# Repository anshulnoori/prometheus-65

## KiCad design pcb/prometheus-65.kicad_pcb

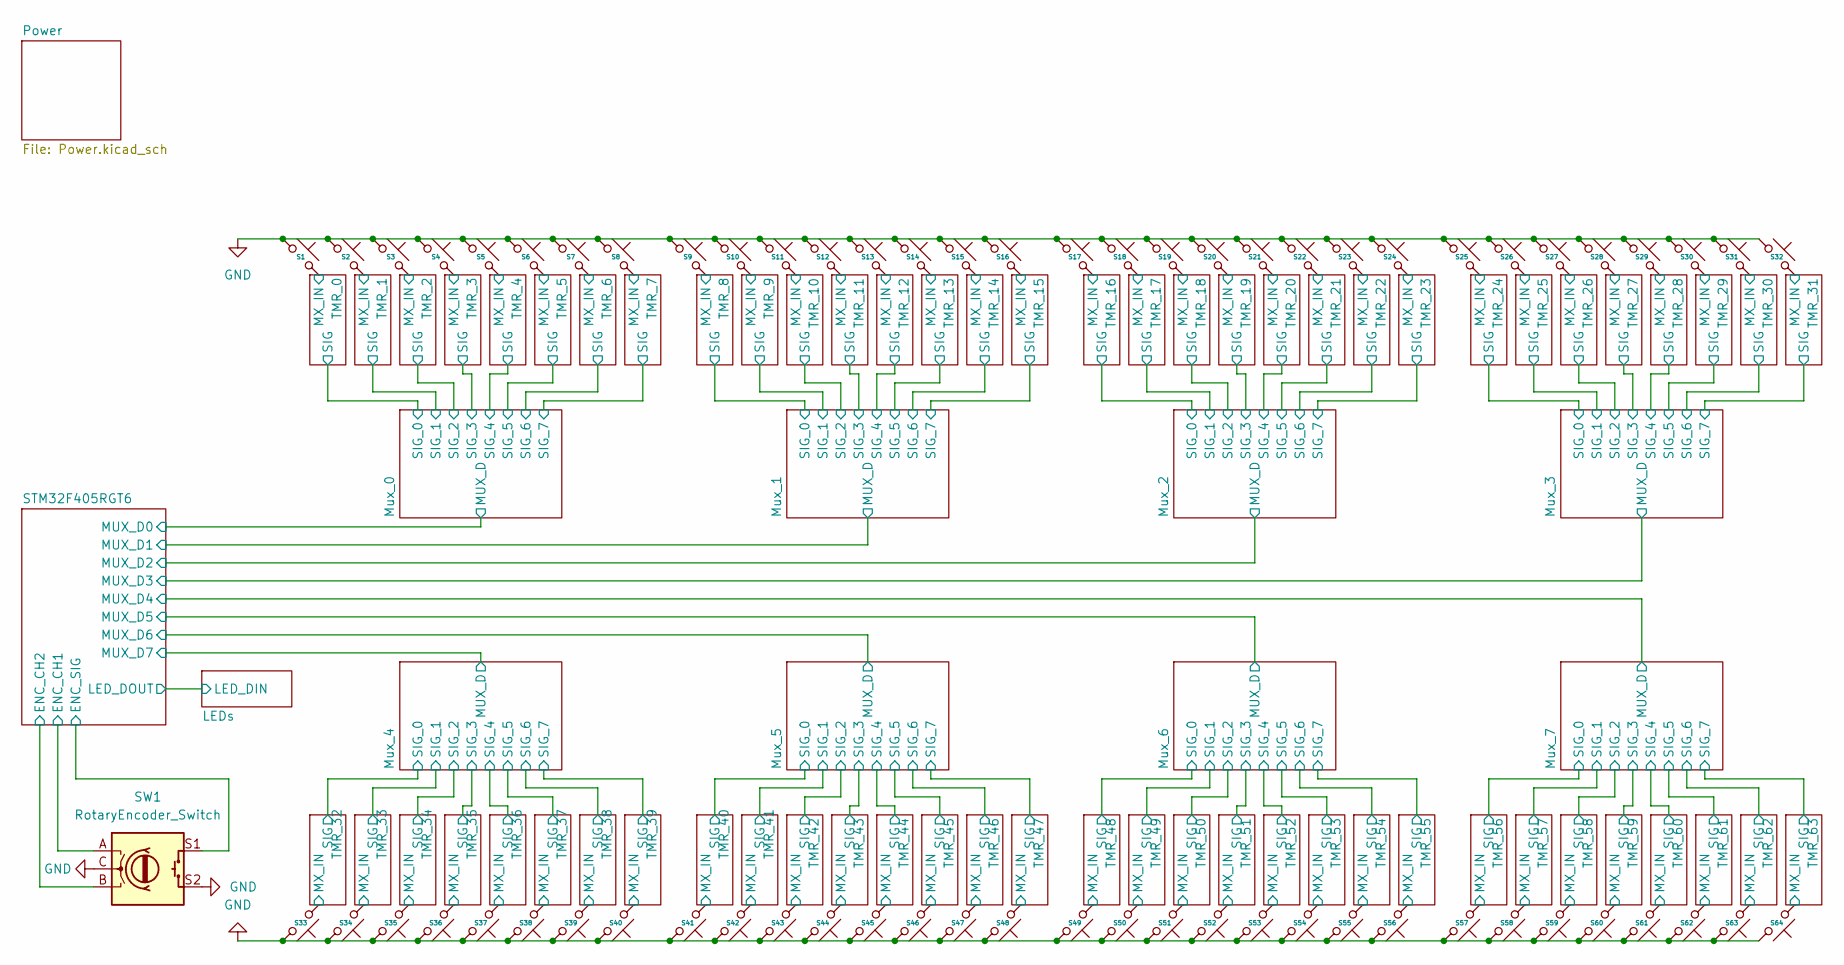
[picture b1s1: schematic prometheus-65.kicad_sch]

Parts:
S1, S2, S3, S4, S6, S7, S9, S10, S12, S13, S17, S18, S19, S20, S21, S22, S23, S24, S25, S26, S27, S28, S29, S30, S31, S33, S34, S35, S36, S37, S38, S39, S40, S41, S42, S43, S44, S45, S46, S47, S49, S50, S51, S53, S54, S55, S58, S60, S64: Hotswap_MX_Plated_1.00u
S5, S56: Hotswap_MX_Plated_1.50u
S8: Hotswap_MX_Plated_1.75u
S11, S57: Hotswap_MX_Plated_2.25u
S14, S15, S16, S48, S61, S62, S63: Hotswap_MX_Plated_1.25u
S32: Hotswap_MX_Plated_6.25u
S52: Hotswap_MX_Plated_2.00u
S59: Hotswap_MX_Plated_2.75u
SW1: RotaryEncoder_Switch; RotaryEncoder_Alps_EC11E-Switch_Vertical_H20mm

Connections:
/Mux_0/SIG_0: S1.2; also elsewhere on the board
/Mux_0/SIG_1: S2.2; also elsewhere on the board
/Mux_0/SIG_2: S3.2; also elsewhere on the board
/Mux_0/SIG_3: S4.2; also elsewhere on the board
/Mux_0/SIG_4: S5.2; also elsewhere on the board
/Mux_0/SIG_5: S6.2; also elsewhere on the board
/Mux_0/SIG_6: S7.2; also elsewhere on the board
/Mux_0/SIG_7: S8.2; also elsewhere on the board
/Mux_1/SIG_0: S9.2; also elsewhere on the board
/Mux_1/SIG_1: S10.2; also elsewhere on the board
/Mux_1/SIG_2: S11.2; also elsewhere on the board
/Mux_1/SIG_3: S12.2; also elsewhere on the board
/Mux_1/SIG_4: S13.2; also elsewhere on the board
/Mux_1/SIG_5: S14.2; also elsewhere on the board
/Mux_1/SIG_6: S15.2; also elsewhere on the board
/Mux_1/SIG_7: S16.2; also elsewhere on the board
/Mux_2/SIG_0: S17.2; also elsewhere on the board
/Mux_2/SIG_1: S18.2; also elsewhere on the board
/Mux_2/SIG_2: S19.2; also elsewhere on the board
/Mux_2/SIG_3: S20.2; also elsewhere on the board
/Mux_2/SIG_4: S21.2; also elsewhere on the board
/Mux_2/SIG_5: S22.2; also elsewhere on the board
/Mux_2/SIG_6: S23.2; also elsewhere on the board
/Mux_2/SIG_7: S24.2; also elsewhere on the board
/Mux_3/SIG_0: S25.2; also elsewhere on the board
/Mux_3/SIG_1: S26.2; also elsewhere on the board
/Mux_3/SIG_2: S27.2; also elsewhere on the board
/Mux_3/SIG_3: S28.2; also elsewhere on the board
/Mux_3/SIG_4: S29.2; also elsewhere on the board
/Mux_3/SIG_5: S30.2; also elsewhere on the board
/Mux_3/SIG_6: S31.2; also elsewhere on the board
/Mux_3/SIG_7: S32.2; also elsewhere on the board
/Mux_4/SIG_0: S33.2; also elsewhere on the board
/Mux_4/SIG_1: S34.2; also elsewhere on the board
/Mux_4/SIG_2: S35.2; also elsewhere on the board
/Mux_4/SIG_3: S36.2; also elsewhere on the board
/Mux_4/SIG_4: S37.2; also elsewhere on the board
/Mux_4/SIG_5: S38.2; also elsewhere on the board
/Mux_4/SIG_6: S39.2; also elsewhere on the board
/Mux_4/SIG_7: S40.2; also elsewhere on the board
/Mux_5/SIG_0: S41.2; also elsewhere on the board
/Mux_5/SIG_1: S42.2; also elsewhere on the board
/Mux_5/SIG_2: S43.2; also elsewhere on the board
/Mux_5/SIG_3: S44.2; also elsewhere on the board
/Mux_5/SIG_4: S45.2; also elsewhere on the board
/Mux_5/SIG_5: S46.2; also elsewhere on the board
/Mux_5/SIG_6: S47.2; also elsewhere on the board
/Mux_5/SIG_7: S48.2; also elsewhere on the board
/Mux_6/SIG_0: S49.2; also elsewhere on the board
/Mux_6/SIG_1: S50.2; also elsewhere on the board
/Mux_6/SIG_2: S51.2; also elsewhere on the board
/Mux_6/SIG_3: S52.2; also elsewhere on the board
/Mux_6/SIG_4: S53.2; also elsewhere on the board
/Mux_6/SIG_5: S54.2; also elsewhere on the board
/Mux_6/SIG_6: S55.2; also elsewhere on the board
/Mux_6/SIG_7: S56.2; also elsewhere on the board
/Mux_7/SIG_0: S57.2; also elsewhere on the board
/Mux_7/SIG_1: S58.2; also elsewhere on the board
/Mux_7/SIG_2: S59.2; also elsewhere on the board
/Mux_7/SIG_3: S60.2; also elsewhere on the board
/Mux_7/SIG_4: S61.2; also elsewhere on the board
/Mux_7/SIG_5: S62.2; also elsewhere on the board
/Mux_7/SIG_6: S63.2; also elsewhere on the board
/Mux_7/SIG_7: S64.2; also elsewhere on the board
/STM32F405RGT6/ENC_CH1: SW1.A; also elsewhere on the board
/STM32F405RGT6/ENC_CH2: SW1.B; also elsewhere on the board
/STM32F405RGT6/ENC_SIG: SW1.S1; also elsewhere on the board

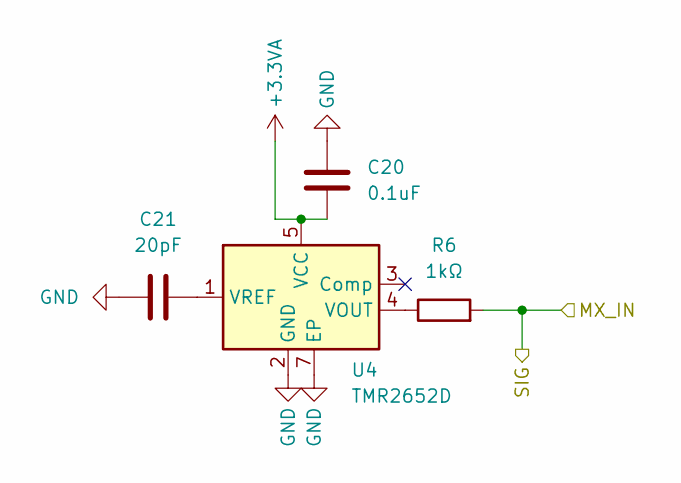
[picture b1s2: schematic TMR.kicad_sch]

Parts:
C20: 0.1uF; C_0402_1005Metric
C21: 20pF; C_0402_1005Metric
R6: 1kΩ; R_0402_1005Metric
U4: TMR2652D

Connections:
/Mux_0/SIG_0: R6.2; also elsewhere on the board
unnamed: R6.1, U4.4 (VOUT)

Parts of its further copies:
C22, C24, C26, C28, C30, C32, C34, C36, C38, C40, C42, C44, C46, C48, C50, C52, C54, C56, C58, C60, C62, C64, C66, C68, C70, C72, C74, C76, C78, C80, C82, C84, C86, C88, C90, C92, C94, C96, C98, C100, C102, C104, C106, C108, C110, C112, C114, C116, C118, C120, C122, C124, C126, C128, C130, C132, C134, C136, C138, C140, C142, C144, C146: 0.1uF; C_0402_1005Metric
C23, C25, C27, C29, C31, C33, C35, C37, C39, C41, C43, C45, C47, C49, C51, C53, C55, C57, C59, C61, C63, C65, C67, C69, C71, C73, C75, C77, C79, C81, C83, C85, C87, C89, C91, C93, C95, C97, C99, C101, C103, C105, C107, C109, C111, C113, C115, C117, C119, C121, C123, C125, C127, C129, C131, C133, C135, C137, C139, C141, C143, C145, C147: 20pF; C_0402_1005Metric
R7, R8, R9, R10, R11, R12, R13, R14, R15, R16, R17, R18, R19, R20, R21, R22, R23, R24, R25, R26, R27, R28, R29, R30, R31, R32, R33, R34, R35, R36, R37, R38, R39, R40, R41, R42, R43, R44, R45, R46, R47, R48, R49, R50, R51, R52, R53, R54, R55, R56, R57, R58, R59, R60, R61, R62, R63, R64, R65, R66, R67, R68, R69: 1kΩ; R_0402_1005Metric
U6, U7, U8, U9, U10, U11, U12, U13, U14, U15, U16, U17, U18, U19, U20, U22, U23, U24, U25, U26, U27, U28, U29, U31, U32, U33, U34, U35, U36, U37, U38, U40, U41, U42, U43, U44, U45, U46, U47, U48, U49, U50, U51, U52, U53, U54, U55, U56, U57, U58, U59, U60, U61, U62, U63, U64, U65, U66, U67, U68, U69, U70, U71: TMR2652D

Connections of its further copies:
/Mux_0/SIG_1: R7.2; also elsewhere on the board
/Mux_0/SIG_2: R8.2; also elsewhere on the board
/Mux_0/SIG_3: R9.2; also elsewhere on the board
/Mux_0/SIG_4: R10.2; also elsewhere on the board
/Mux_0/SIG_5: R11.2; also elsewhere on the board
/Mux_0/SIG_6: R12.2; also elsewhere on the board
/Mux_0/SIG_7: R13.2; also elsewhere on the board
/Mux_1/SIG_0: R14.2; also elsewhere on the board
/Mux_1/SIG_1: R15.2; also elsewhere on the board
/Mux_1/SIG_2: R16.2; also elsewhere on the board
/Mux_1/SIG_3: R17.2; also elsewhere on the board
/Mux_1/SIG_4: R18.2; also elsewhere on the board
/Mux_1/SIG_5: R19.2; also elsewhere on the board
/Mux_1/SIG_6: R20.2; also elsewhere on the board
/Mux_1/SIG_7: R21.2; also elsewhere on the board
/Mux_2/SIG_0: R22.2; also elsewhere on the board
/Mux_2/SIG_1: R23.2; also elsewhere on the board
/Mux_2/SIG_2: R24.2; also elsewhere on the board
/Mux_2/SIG_3: R25.2; also elsewhere on the board
/Mux_2/SIG_4: R26.2; also elsewhere on the board
/Mux_2/SIG_5: R27.2; also elsewhere on the board
/Mux_2/SIG_6: R28.2; also elsewhere on the board
/Mux_2/SIG_7: R29.2; also elsewhere on the board
/Mux_3/SIG_0: R30.2; also elsewhere on the board
/Mux_3/SIG_1: R31.2; also elsewhere on the board
/Mux_3/SIG_2: R32.2; also elsewhere on the board
/Mux_3/SIG_3: R33.2; also elsewhere on the board
/Mux_3/SIG_4: R34.2; also elsewhere on the board
/Mux_3/SIG_5: R35.2; also elsewhere on the board
/Mux_3/SIG_6: R36.2; also elsewhere on the board
/Mux_3/SIG_7: R37.2; also elsewhere on the board
/Mux_4/SIG_0: R38.2; also elsewhere on the board
/Mux_4/SIG_1: R39.2; also elsewhere on the board
/Mux_4/SIG_2: R40.2; also elsewhere on the board
/Mux_4/SIG_3: R41.2; also elsewhere on the board
/Mux_4/SIG_4: R42.2; also elsewhere on the board
/Mux_4/SIG_5: R43.2; also elsewhere on the board
/Mux_4/SIG_6: R44.2; also elsewhere on the board
/Mux_4/SIG_7: R45.2; also elsewhere on the board
/Mux_5/SIG_0: R46.2; also elsewhere on the board
/Mux_5/SIG_1: R47.2; also elsewhere on the board
/Mux_5/SIG_2: R48.2; also elsewhere on the board
/Mux_5/SIG_3: R49.2; also elsewhere on the board
/Mux_5/SIG_4: R50.2; also elsewhere on the board
/Mux_5/SIG_5: R51.2; also elsewhere on the board
/Mux_5/SIG_6: R52.2; also elsewhere on the board
/Mux_5/SIG_7: R53.2; also elsewhere on the board
/Mux_6/SIG_0: R54.2; also elsewhere on the board
/Mux_6/SIG_1: R55.2; also elsewhere on the board
/Mux_6/SIG_2: R56.2; also elsewhere on the board
/Mux_6/SIG_3: R57.2; also elsewhere on the board
/Mux_6/SIG_4: R58.2; also elsewhere on the board
/Mux_6/SIG_5: R59.2; also elsewhere on the board
/Mux_6/SIG_6: R60.2; also elsewhere on the board
/Mux_6/SIG_7: R61.2; also elsewhere on the board
/Mux_7/SIG_0: R62.2; also elsewhere on the board
/Mux_7/SIG_1: R63.2; also elsewhere on the board
/Mux_7/SIG_2: R64.2; also elsewhere on the board
/Mux_7/SIG_3: R65.2; also elsewhere on the board
/Mux_7/SIG_4: R66.2; also elsewhere on the board
/Mux_7/SIG_5: R67.2; also elsewhere on the board
/Mux_7/SIG_6: R68.2; also elsewhere on the board
/Mux_7/SIG_7: R69.2; also elsewhere on the board
unnamed: R7.1, U6.4 (VOUT)
unnamed: C23.2, U6.1 (VREF)
unnamed: R8.1, U7.4 (VOUT)
unnamed: C25.2, U7.1 (VREF)
unnamed: R9.1, U8.4 (VOUT)
unnamed: C27.2, U8.1 (VREF)
unnamed: R10.1, U9.4 (VOUT)
unnamed: C29.2, U9.1 (VREF)
unnamed: R11.1, U10.4 (VOUT)
unnamed: C31.2, U10.1 (VREF)
unnamed: R12.1, U11.4 (VOUT)
unnamed: C33.2, U11.1 (VREF)
unnamed: R13.1, U12.4 (VOUT)
unnamed: C35.2, U12.1 (VREF)
unnamed: R14.1, U13.4 (VOUT)
unnamed: C37.2, U13.1 (VREF)
unnamed: R15.1, U14.4 (VOUT)
unnamed: C39.2, U14.1 (VREF)
unnamed: R16.1, U15.4 (VOUT)
unnamed: C41.2, U15.1 (VREF)
unnamed: R17.1, U16.4 (VOUT)
unnamed: C43.2, U16.1 (VREF)
unnamed: R18.1, U17.4 (VOUT)
unnamed: C45.2, U17.1 (VREF)
unnamed: R19.1, U18.4 (VOUT)
unnamed: C47.2, U18.1 (VREF)
unnamed: R20.1, U19.4 (VOUT)
unnamed: C49.2, U19.1 (VREF)
unnamed: R21.1, U20.4 (VOUT)
unnamed: C51.2, U20.1 (VREF)
unnamed: R22.1, U22.4 (VOUT)
unnamed: C53.2, U22.1 (VREF)
unnamed: R23.1, U23.4 (VOUT)
unnamed: C55.2, U23.1 (VREF)
unnamed: R24.1, U24.4 (VOUT)
unnamed: C57.2, U24.1 (VREF)
unnamed: R25.1, U25.4 (VOUT)
unnamed: C59.2, U25.1 (VREF)
unnamed: R26.1, U26.4 (VOUT)
unnamed: C61.2, U26.1 (VREF)
unnamed: R27.1, U27.4 (VOUT)
unnamed: C63.2, U27.1 (VREF)
unnamed: R28.1, U28.4 (VOUT)
unnamed: C65.2, U28.1 (VREF)
unnamed: R29.1, U29.4 (VOUT)
unnamed: C67.2, U29.1 (VREF)
unnamed: R30.1, U31.4 (VOUT)
unnamed: C69.2, U31.1 (VREF)
unnamed: R31.1, U32.4 (VOUT)
unnamed: C71.2, U32.1 (VREF)
unnamed: R32.1, U33.4 (VOUT)
unnamed: C73.2, U33.1 (VREF)
unnamed: R33.1, U34.4 (VOUT)
unnamed: C75.2, U34.1 (VREF)
unnamed: R34.1, U35.4 (VOUT)
unnamed: C77.2, U35.1 (VREF)
unnamed: R35.1, U36.4 (VOUT)
unnamed: C79.2, U36.1 (VREF)
unnamed: R36.1, U37.4 (VOUT)
unnamed: C81.2, U37.1 (VREF)
unnamed: R37.1, U38.4 (VOUT)
unnamed: C83.2, U38.1 (VREF)
unnamed: R38.1, U40.4 (VOUT)
unnamed: C85.2, U40.1 (VREF)
unnamed: R39.1, U41.4 (VOUT)
unnamed: C87.2, U41.1 (VREF)
unnamed: R40.1, U42.4 (VOUT)
unnamed: C89.2, U42.1 (VREF)
unnamed: R41.1, U43.4 (VOUT)
unnamed: C91.2, U43.1 (VREF)
unnamed: R42.1, U44.4 (VOUT)
unnamed: C93.2, U44.1 (VREF)
unnamed: R43.1, U45.4 (VOUT)
unnamed: C95.2, U45.1 (VREF)
unnamed: R44.1, U46.4 (VOUT)
unnamed: C97.2, U46.1 (VREF)
unnamed: R45.1, U47.4 (VOUT)
unnamed: C99.2, U47.1 (VREF)
unnamed: R46.1, U48.4 (VOUT)
unnamed: C101.2, U48.1 (VREF)
unnamed: R47.1, U49.4 (VOUT)
unnamed: C103.2, U49.1 (VREF)
unnamed: R48.1, U50.4 (VOUT)
unnamed: C105.2, U50.1 (VREF)
unnamed: R49.1, U51.4 (VOUT)
unnamed: C107.2, U51.1 (VREF)
unnamed: R50.1, U52.4 (VOUT)
unnamed: C109.2, U52.1 (VREF)
unnamed: R51.1, U53.4 (VOUT)
unnamed: C111.2, U53.1 (VREF)
unnamed: R52.1, U54.4 (VOUT)
unnamed: C113.2, U54.1 (VREF)
unnamed: R53.1, U55.4 (VOUT)
unnamed: C115.2, U55.1 (VREF)
unnamed: R54.1, U56.4 (VOUT)
unnamed: C117.2, U56.1 (VREF)
unnamed: R55.1, U57.4 (VOUT)
unnamed: C119.2, U57.1 (VREF)
unnamed: R56.1, U58.4 (VOUT)
unnamed: C121.2, U58.1 (VREF)
unnamed: R57.1, U59.4 (VOUT)
unnamed: C123.2, U59.1 (VREF)
unnamed: R58.1, U60.4 (VOUT)
unnamed: C125.2, U60.1 (VREF)
unnamed: R59.1, U61.4 (VOUT)
unnamed: C127.2, U61.1 (VREF)
unnamed: R60.1, U62.4 (VOUT)
unnamed: C129.2, U62.1 (VREF)
unnamed: R61.1, U63.4 (VOUT)
unnamed: C131.2, U63.1 (VREF)
unnamed: R62.1, U64.4 (VOUT)
unnamed: C133.2, U64.1 (VREF)
unnamed: R63.1, U65.4 (VOUT)
unnamed: C135.2, U65.1 (VREF)
unnamed: R64.1, U66.4 (VOUT)
unnamed: C137.2, U66.1 (VREF)
unnamed: R65.1, U67.4 (VOUT)
unnamed: C139.2, U67.1 (VREF)
unnamed: R66.1, U68.4 (VOUT)
unnamed: C141.2, U68.1 (VREF)
unnamed: R67.1, U69.4 (VOUT)
unnamed: C143.2, U69.1 (VREF)
unnamed: R68.1, U70.4 (VOUT)
unnamed: C145.2, U70.1 (VREF)
unnamed: R69.1, U71.4 (VOUT)
unnamed: C147.2, U71.1 (VREF)

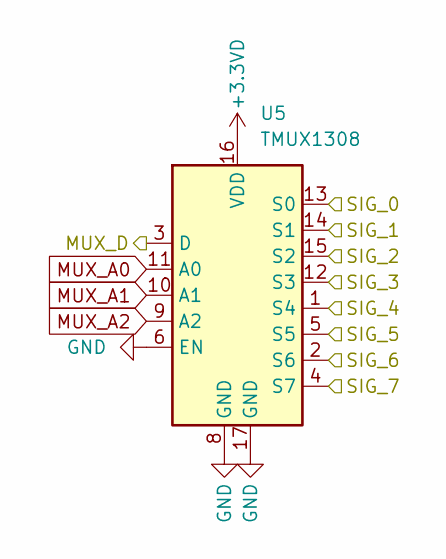
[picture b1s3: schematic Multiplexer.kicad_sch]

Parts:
U5: TMUX1308; TMUX1308BQBR

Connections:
/Mux_0/MUX_D: U5.3 (D); also elsewhere on the board
/Mux_0/SIG_0: U5.13 (S0); also elsewhere on the board
/Mux_0/SIG_1: U5.14 (S1); also elsewhere on the board
/Mux_0/SIG_2: U5.15 (S2); also elsewhere on the board
/Mux_0/SIG_3: U5.12 (S3); also elsewhere on the board
/Mux_0/SIG_4: U5.1 (S4); also elsewhere on the board
/Mux_0/SIG_5: U5.5 (S5); also elsewhere on the board
/Mux_0/SIG_6: U5.2 (S6); also elsewhere on the board
/Mux_0/SIG_7: U5.4 (S7); also elsewhere on the board
MUX_A0: U5.11 (A0); also elsewhere on the board
MUX_A1: U5.10 (A1); also elsewhere on the board
MUX_A2: U5.9 (A2); also elsewhere on the board

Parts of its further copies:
U21, U30, U39, U72, U73, U74, U75: TMUX1308; TMUX1308BQBR

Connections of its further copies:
/Mux_1/MUX_D: U21.3 (D); also elsewhere on the board
/Mux_1/SIG_0: U21.13 (S0); also elsewhere on the board
/Mux_1/SIG_1: U21.14 (S1); also elsewhere on the board
/Mux_1/SIG_2: U21.15 (S2); also elsewhere on the board
/Mux_1/SIG_3: U21.12 (S3); also elsewhere on the board
/Mux_1/SIG_4: U21.1 (S4); also elsewhere on the board
/Mux_1/SIG_5: U21.5 (S5); also elsewhere on the board
/Mux_1/SIG_6: U21.2 (S6); also elsewhere on the board
/Mux_1/SIG_7: U21.4 (S7); also elsewhere on the board
/Mux_2/MUX_D: U30.3 (D); also elsewhere on the board
/Mux_2/SIG_0: U30.13 (S0); also elsewhere on the board
/Mux_2/SIG_1: U30.14 (S1); also elsewhere on the board
/Mux_2/SIG_2: U30.15 (S2); also elsewhere on the board
/Mux_2/SIG_3: U30.12 (S3); also elsewhere on the board
/Mux_2/SIG_4: U30.1 (S4); also elsewhere on the board
/Mux_2/SIG_5: U30.5 (S5); also elsewhere on the board
/Mux_2/SIG_6: U30.2 (S6); also elsewhere on the board
/Mux_2/SIG_7: U30.4 (S7); also elsewhere on the board
/Mux_3/MUX_D: U39.3 (D); also elsewhere on the board
/Mux_3/SIG_0: U39.13 (S0); also elsewhere on the board
/Mux_3/SIG_1: U39.14 (S1); also elsewhere on the board
/Mux_3/SIG_2: U39.15 (S2); also elsewhere on the board
/Mux_3/SIG_3: U39.12 (S3); also elsewhere on the board
/Mux_3/SIG_4: U39.1 (S4); also elsewhere on the board
/Mux_3/SIG_5: U39.5 (S5); also elsewhere on the board
/Mux_3/SIG_6: U39.2 (S6); also elsewhere on the board
/Mux_3/SIG_7: U39.4 (S7); also elsewhere on the board
/Mux_4/MUX_D: U72.3 (D); also elsewhere on the board
/Mux_4/SIG_0: U72.13 (S0); also elsewhere on the board
/Mux_4/SIG_1: U72.14 (S1); also elsewhere on the board
/Mux_4/SIG_2: U72.15 (S2); also elsewhere on the board
/Mux_4/SIG_3: U72.12 (S3); also elsewhere on the board
/Mux_4/SIG_4: U72.1 (S4); also elsewhere on the board
/Mux_4/SIG_5: U72.5 (S5); also elsewhere on the board
/Mux_4/SIG_6: U72.2 (S6); also elsewhere on the board
/Mux_4/SIG_7: U72.4 (S7); also elsewhere on the board
/Mux_5/MUX_D: U73.3 (D); also elsewhere on the board
/Mux_5/SIG_0: U73.13 (S0); also elsewhere on the board
/Mux_5/SIG_1: U73.14 (S1); also elsewhere on the board
/Mux_5/SIG_2: U73.15 (S2); also elsewhere on the board
/Mux_5/SIG_3: U73.12 (S3); also elsewhere on the board
/Mux_5/SIG_4: U73.1 (S4); also elsewhere on the board
/Mux_5/SIG_5: U73.5 (S5); also elsewhere on the board
/Mux_5/SIG_6: U73.2 (S6); also elsewhere on the board
/Mux_5/SIG_7: U73.4 (S7); also elsewhere on the board
/Mux_6/MUX_D: U74.3 (D); also elsewhere on the board
/Mux_6/SIG_0: U74.13 (S0); also elsewhere on the board
/Mux_6/SIG_1: U74.14 (S1); also elsewhere on the board
/Mux_6/SIG_2: U74.15 (S2); also elsewhere on the board
/Mux_6/SIG_3: U74.12 (S3); also elsewhere on the board
/Mux_6/SIG_4: U74.1 (S4); also elsewhere on the board
/Mux_6/SIG_5: U74.5 (S5); also elsewhere on the board
/Mux_6/SIG_6: U74.2 (S6); also elsewhere on the board
/Mux_6/SIG_7: U74.4 (S7); also elsewhere on the board
/Mux_7/MUX_D: U75.3 (D); also elsewhere on the board
/Mux_7/SIG_0: U75.13 (S0); also elsewhere on the board
/Mux_7/SIG_1: U75.14 (S1); also elsewhere on the board
/Mux_7/SIG_2: U75.15 (S2); also elsewhere on the board
/Mux_7/SIG_3: U75.12 (S3); also elsewhere on the board
/Mux_7/SIG_4: U75.1 (S4); also elsewhere on the board
/Mux_7/SIG_5: U75.5 (S5); also elsewhere on the board
/Mux_7/SIG_6: U75.2 (S6); also elsewhere on the board
/Mux_7/SIG_7: U75.4 (S7); also elsewhere on the board
MUX_A0: U21.11 (A0), U30.11 (A0), U39.11 (A0), U72.11 (A0), U73.11 (A0), U74.11 (A0), U75.11 (A0); also elsewhere on the board
MUX_A1: U21.10 (A1), U30.10 (A1), U39.10 (A1), U72.10 (A1), U73.10 (A1), U74.10 (A1), U75.10 (A1); also elsewhere on the board
MUX_A2: U21.9 (A2), U30.9 (A2), U39.9 (A2), U72.9 (A2), U73.9 (A2), U74.9 (A2), U75.9 (A2); also elsewhere on the board

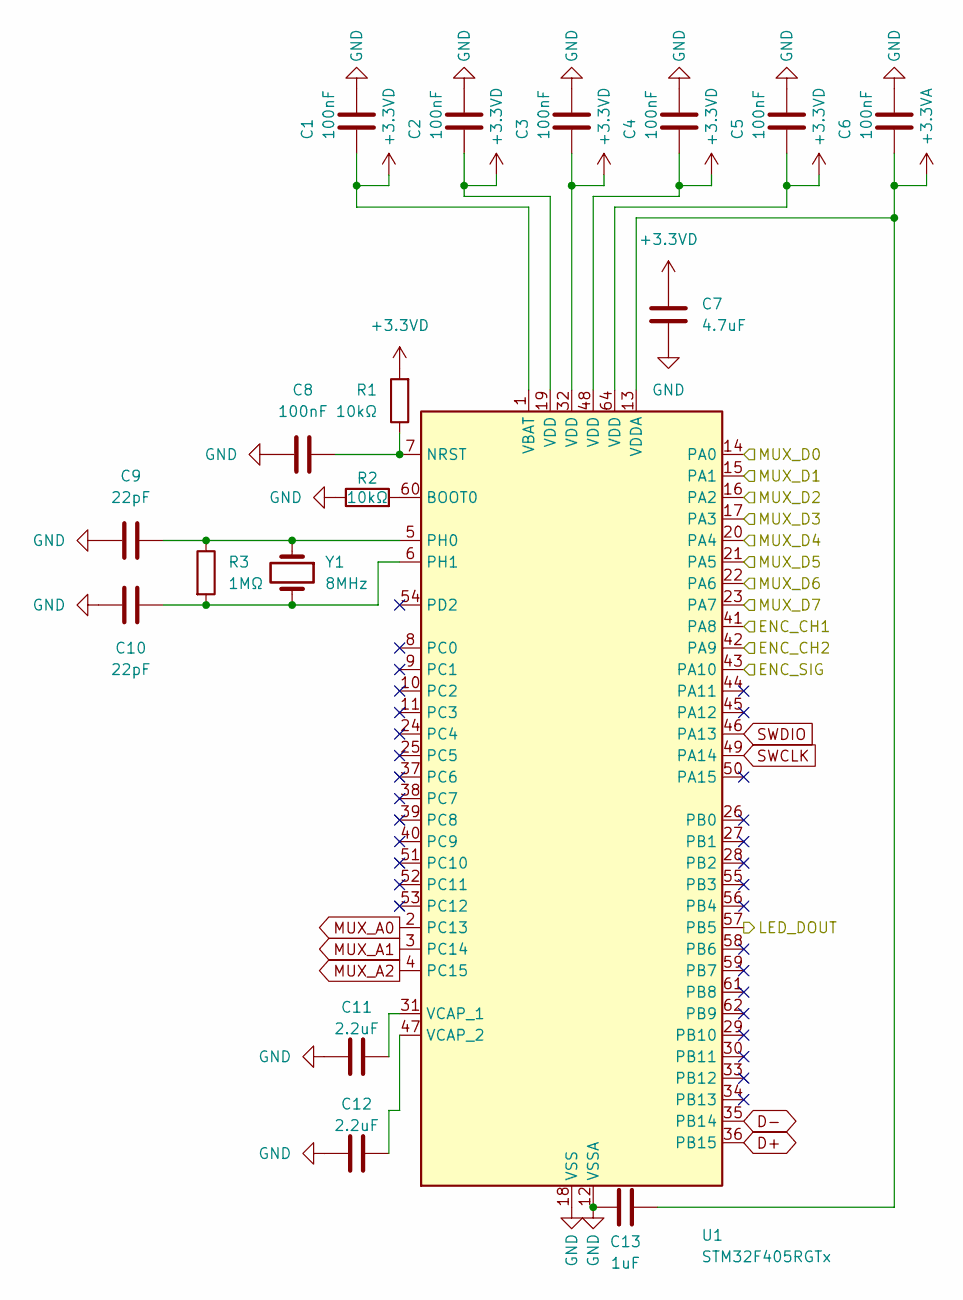
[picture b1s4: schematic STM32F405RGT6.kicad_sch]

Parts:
C1, C2, C3, C4, C5, C6, C8: 100nF; C_0402_1005Metric
C7: 4.7uF; C_0603_1608Metric
C9, C10: 22pF; C_0402_1005Metric
C11, C12: 2.2uF; C_0603_1608Metric
C13: 1uF; C_0603_1608Metric
R1, R2: 10kΩ; R_0603_1608Metric
R3: 1MΩ; R_0603_1608Metric
U1: STM32F405RGTx; LQFP-64_10x10mm_P0.5mm
Y1: 8MHz; Crystal_SMD_3225-4Pin_3.2x2.5mm

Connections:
/LEDs/LED_DIN: U1.57 (PB5); also elsewhere on the board
/Mux_0/MUX_D: U1.14 (PA0); also elsewhere on the board
/Mux_1/MUX_D: U1.15 (PA1); also elsewhere on the board
/Mux_2/MUX_D: U1.16 (PA2); also elsewhere on the board
/Mux_3/MUX_D: U1.17 (PA3); also elsewhere on the board
/Mux_4/MUX_D: U1.23 (PA7); also elsewhere on the board
/Mux_5/MUX_D: U1.22 (PA6); also elsewhere on the board
/Mux_6/MUX_D: U1.21 (PA5); also elsewhere on the board
/Mux_7/MUX_D: U1.20 (PA4); also elsewhere on the board
/STM32F405RGT6/ENC_CH1: U1.41 (PA8); also elsewhere on the board
/STM32F405RGT6/ENC_CH2: U1.42 (PA9); also elsewhere on the board
/STM32F405RGT6/ENC_SIG: U1.43 (PA10); also elsewhere on the board
D+: U1.36 (PB15); also elsewhere on the board
D-: U1.35 (PB14); also elsewhere on the board
MUX_A0: U1.2 (PC13); also elsewhere on the board
MUX_A1: U1.3 (PC14); also elsewhere on the board
MUX_A2: U1.4 (PC15); also elsewhere on the board
unnamed: R2.2, U1.60 (BOOT0)
unnamed: C8.2, R1.1, U1.7 (NRST)
unnamed: C10.2, R3.2, U1.6 (PH1), Y1.2
unnamed: C11.2, U1.31 (VCAP_1)
unnamed: C12.2, U1.47 (VCAP_2)
SWCLK: U1.49 (PA14)
SWDIO: U1.46 (PA13)

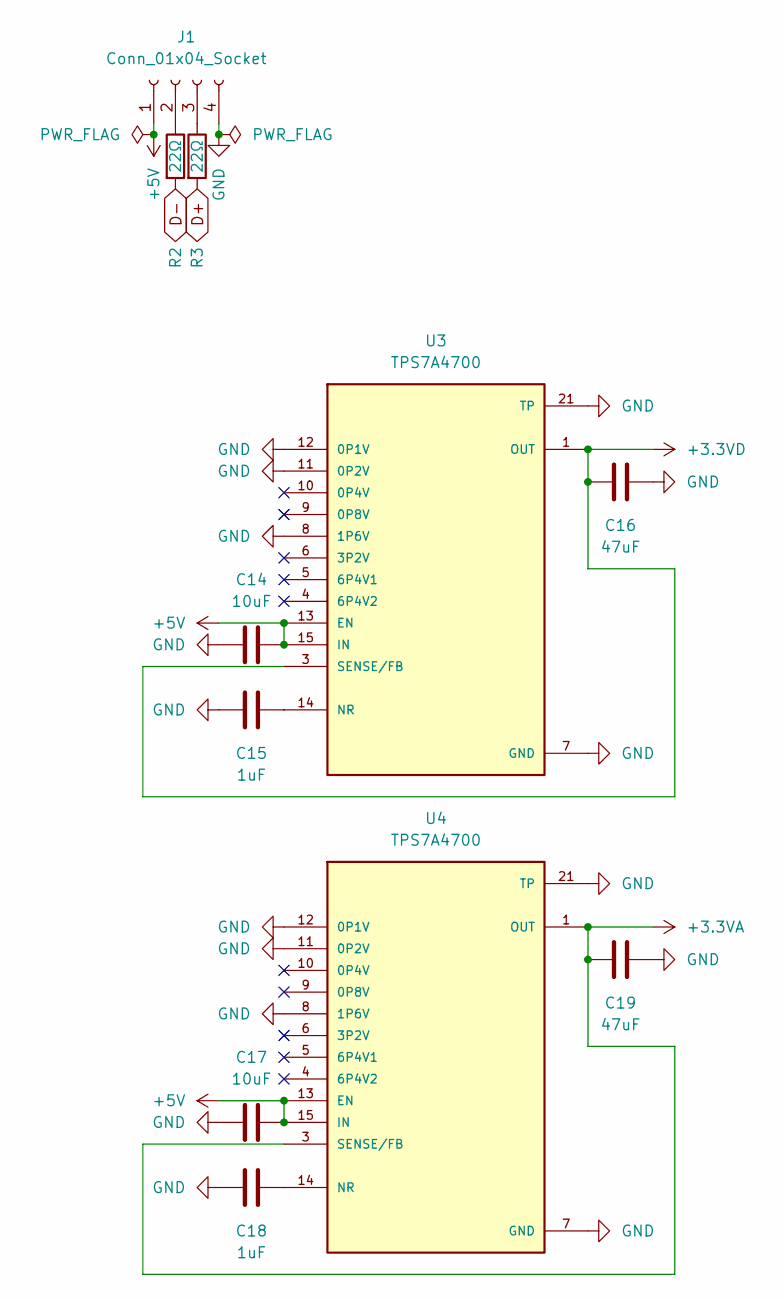
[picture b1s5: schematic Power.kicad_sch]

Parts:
C14, C17: 10uF
C15, C18: 1uF
C16, C19: 47uF
J1: Conn_01x04_Socket
R2, R3: 22Ω
U3, U4: TPS7A4700; TPS7A47000RGWT

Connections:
unnamed 146: R2.2; also elsewhere on the board
unnamed 148: R3.2; also elsewhere on the board
unnamed 151: U4.4 (VOUT); also elsewhere on the board

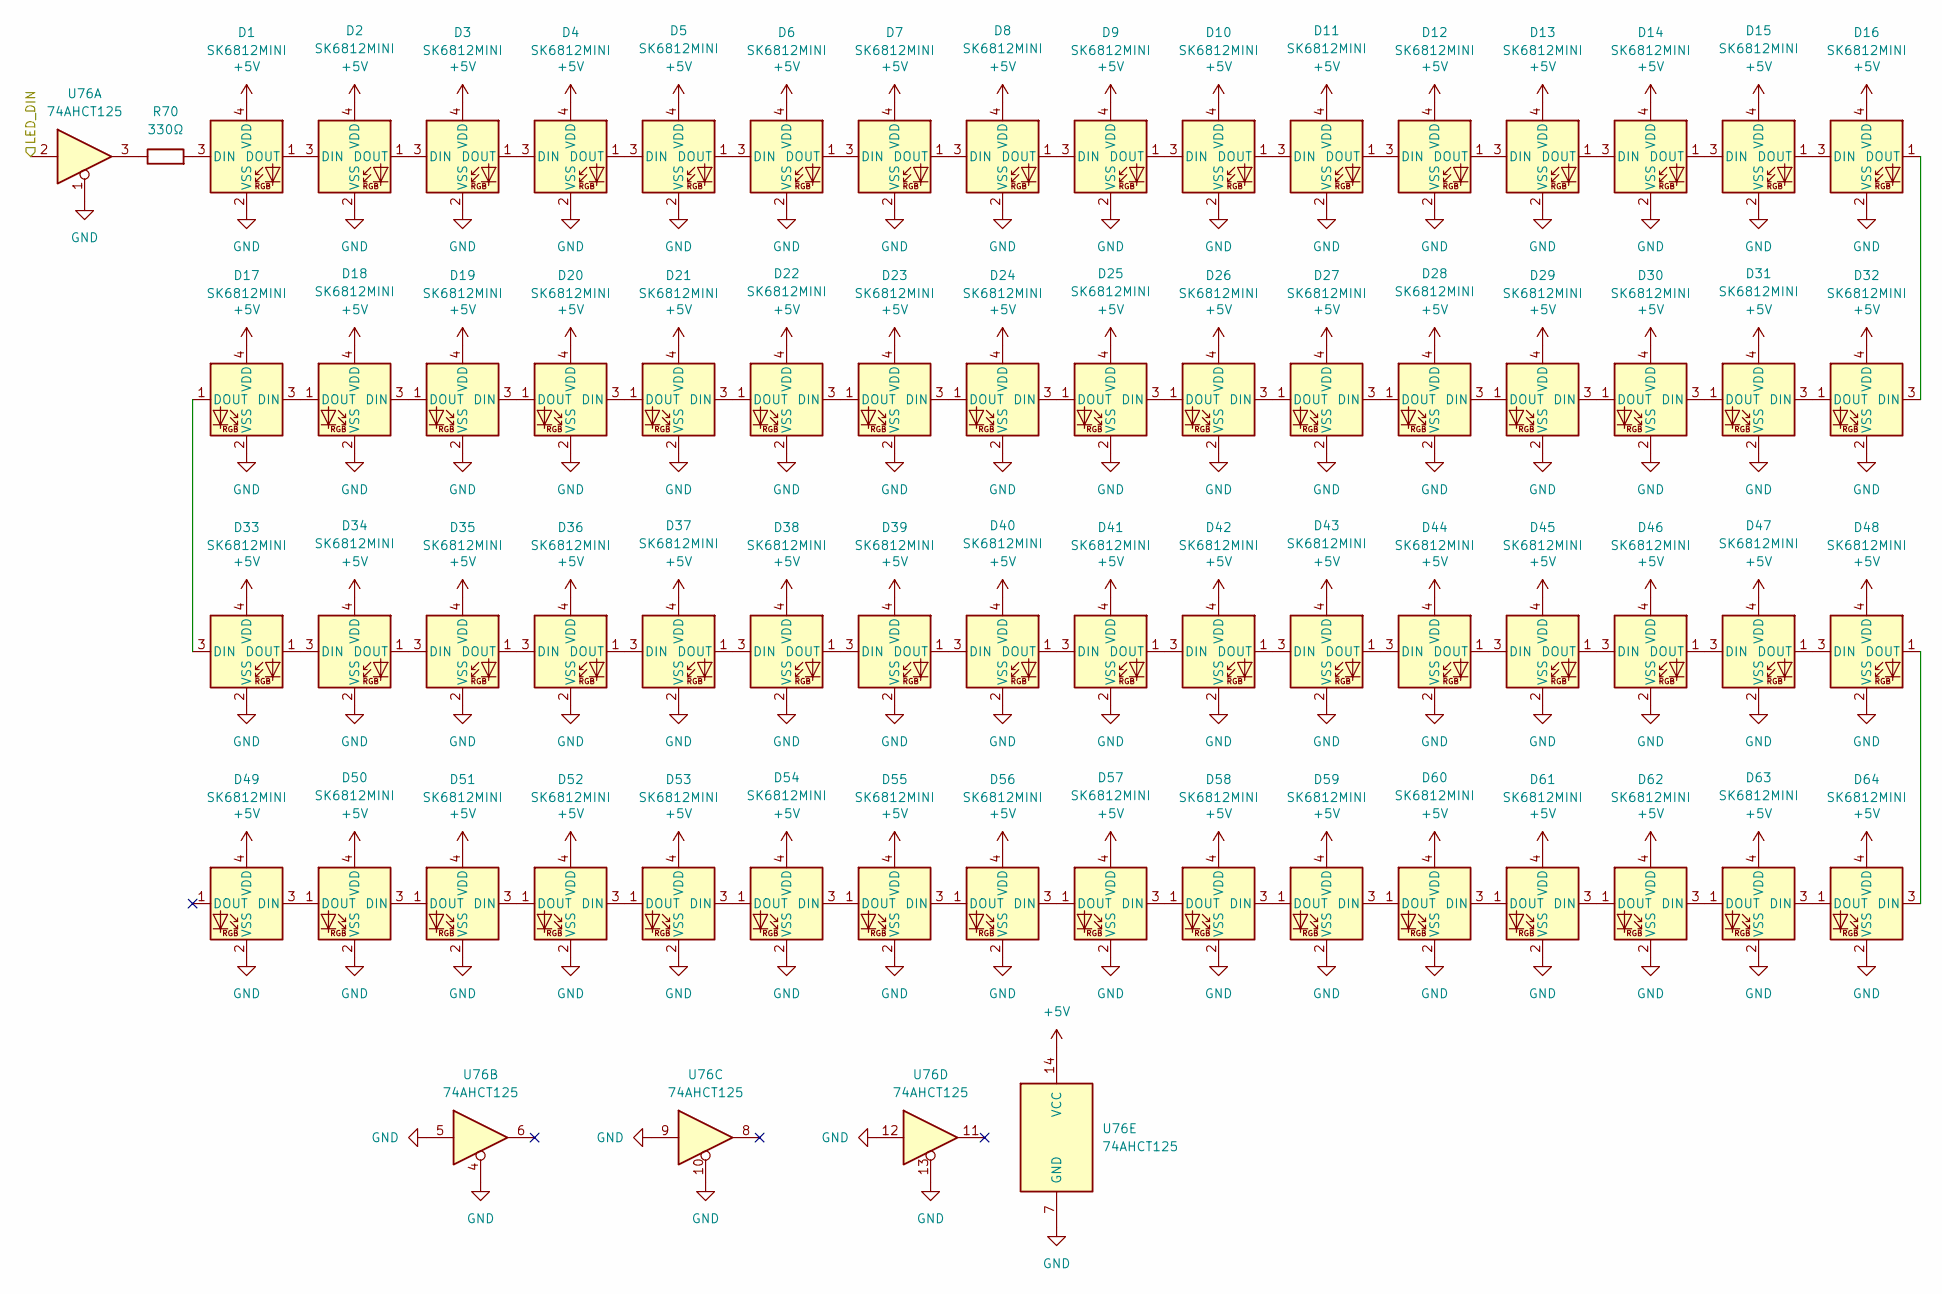
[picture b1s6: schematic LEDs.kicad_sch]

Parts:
D1, D2, D3, D4, D5, D6, D7, D8, D9, D10, D11, D12, D13, D14, D15, D16, D17, D18, D19, D20, D21, D22, D23, D24, D25, D26, D27, D28, D29, D30, D31, D32, D33, D34, D35, D36, D37, D38, D39, D40, D41, D42, D43, D44, D45, D46, D47, D48, D49, D50, D51, D52, D53, D54, D55, D56, D57, D58, D59, D60, D61, D62, D63, D64: SK6812MINI; LED_SK6812MINI_PLCC4_3.5x3.5mm_P1.75mm
R70: 330Ω; R_0603_1608Metric
U76: 74AHCT125; SN74AUC08RGYRG4

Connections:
/LEDs/LED_DIN: U76.2; also elsewhere on the board
unnamed: D1.3 (DIN), R70.2
unnamed: D1.1 (DOUT), D2.3 (DIN)
unnamed: D2.1 (DOUT), D3.3 (DIN)
unnamed: D3.1 (DOUT), D4.3 (DIN)
unnamed: D4.1 (DOUT), D5.3 (DIN)
unnamed: D5.1 (DOUT), D6.3 (DIN)
unnamed: D6.1 (DOUT), D7.3 (DIN)
unnamed: D7.1 (DOUT), D8.3 (DIN)
unnamed: D8.1 (DOUT), D9.3 (DIN)
unnamed: D9.1 (DOUT), D10.3 (DIN)
unnamed: D10.1 (DOUT), D11.3 (DIN)
unnamed: D11.1 (DOUT), D12.3 (DIN)
unnamed: D12.1 (DOUT), D13.3 (DIN)
unnamed: D13.1 (DOUT), D14.3 (DIN)
unnamed: D14.1 (DOUT), D15.3 (DIN)
unnamed: D15.1 (DOUT), D16.3 (DIN)
unnamed: D16.1 (DOUT), D32.3 (DIN)
unnamed: D17.3 (DIN), D18.1 (DOUT)
unnamed: D17.1 (DOUT), D33.3 (DIN)
unnamed: D18.3 (DIN), D19.1 (DOUT)
unnamed: D19.3 (DIN), D20.1 (DOUT)
unnamed: D20.3 (DIN), D21.1 (DOUT)
unnamed: D21.3 (DIN), D22.1 (DOUT)
unnamed: D22.3 (DIN), D23.1 (DOUT)
unnamed: D23.3 (DIN), D24.1 (DOUT)
unnamed: D24.3 (DIN), D25.1 (DOUT)
unnamed: D25.3 (DIN), D26.1 (DOUT)
unnamed: D26.3 (DIN), D27.1 (DOUT)
unnamed: D27.3 (DIN), D28.1 (DOUT)
unnamed: D28.3 (DIN), D29.1 (DOUT)
unnamed: D29.3 (DIN), D30.1 (DOUT)
unnamed: D30.3 (DIN), D31.1 (DOUT)
unnamed: D31.3 (DIN), D32.1 (DOUT)
unnamed: D33.1 (DOUT), D34.3 (DIN)
unnamed: D34.1 (DOUT), D35.3 (DIN)
unnamed: D35.1 (DOUT), D36.3 (DIN)
unnamed: D36.1 (DOUT), D37.3 (DIN)
unnamed: D37.1 (DOUT), D38.3 (DIN)
unnamed: D38.1 (DOUT), D39.3 (DIN)
unnamed: D39.1 (DOUT), D40.3 (DIN)
unnamed: D40.1 (DOUT), D41.3 (DIN)
unnamed: D41.1 (DOUT), D42.3 (DIN)
unnamed: D42.1 (DOUT), D43.3 (DIN)
unnamed: D43.1 (DOUT), D44.3 (DIN)
unnamed: D44.1 (DOUT), D45.3 (DIN)
unnamed: D45.1 (DOUT), D46.3 (DIN)
unnamed: D46.1 (DOUT), D47.3 (DIN)
unnamed: D47.1 (DOUT), D48.3 (DIN)
unnamed: D48.1 (DOUT), D64.3 (DIN)
unnamed: D49.3 (DIN), D50.1 (DOUT)
unnamed: D50.3 (DIN), D51.1 (DOUT)
unnamed: D51.3 (DIN), D52.1 (DOUT)
unnamed: D52.3 (DIN), D53.1 (DOUT)
unnamed: D53.3 (DIN), D54.1 (DOUT)
unnamed: D54.3 (DIN), D55.1 (DOUT)
unnamed: D55.3 (DIN), D56.1 (DOUT)
unnamed: D56.3 (DIN), D57.1 (DOUT)
unnamed: D57.3 (DIN), D58.1 (DOUT)
unnamed: D58.3 (DIN), D59.1 (DOUT)
unnamed: D59.3 (DIN), D60.1 (DOUT)
unnamed: D60.3 (DIN), D61.1 (DOUT)
unnamed: D61.3 (DIN), D62.1 (DOUT)
unnamed: D62.3 (DIN), D63.1 (DOUT)
unnamed: D63.3 (DIN), D64.1 (DOUT)
unnamed: R70.1, U76.3

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
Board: 4 copper layers, 424 parts (20 on the bottom side), 288 nets, no tracks yet.

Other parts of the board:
R4, R5: 22Ω; R_0603_1608Metric
U2: TPS7A4700; TPS7A47000RGWT

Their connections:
D+: R5.2; also elsewhere on the board
D-: R4.2; also elsewhere on the board

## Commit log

2025-12-23 ci: added a commit standard following @conventional-commits
2025-12-23 feat: added qmk_firmware and started kicad project
2025-12-23 refactor: added a GPL license, and updated package.json accordingly
2025-12-24 feat: created a KiCad symbol and footprint for the TMR2652D-P3 sensor
2025-12-24 feat: added keyboard layout file and preview images
2025-12-24 fix: fixed the footprint for the TMR2652D, added a 3d model, and linked it to the respective symbol
2025-12-24 feat: add symbol, footprint, and 3d model for TMUX1308
2025-12-25 build: add MX switch library by @joe-scotto
2025-12-25 feat: started wiring the schematic, and added the STM32 datasheet
2025-12-25 fix: update duplicate label names, and fix directions
2025-12-26 feat: added power, clock, usb header, and SWD circuits to STM32, added symbol, footprint, and 3d model for TPS7A47000RGWT from SnapEda
2025-12-26 feat: added TPS7A4700RGWT LDOs for power circuit
2025-12-26 feat: added key circuit and wired 64 keys
2025-12-26 test: ensure key circuit is theoretically correct
2025-12-26 docs: added datasheet for TPS7A4700RGWT
2025-12-26 refactor: move /hardware to /pcb and delete unused symbols
2025-12-26 feat: added the rotary encoder
2025-12-26 fix: moved D- and D+ to PB14 and PB15 for USB High Speed rather
2025-12-26 feat: added LED circuit and wired to STM32
2025-12-26 style: adjust spacing in schematic
2025-12-27 feat: assigned footprints for each symbol and switch
2025-12-27 feat: created PCB, organized switches into the proper 64 key layout, and started TMR sensor placement
